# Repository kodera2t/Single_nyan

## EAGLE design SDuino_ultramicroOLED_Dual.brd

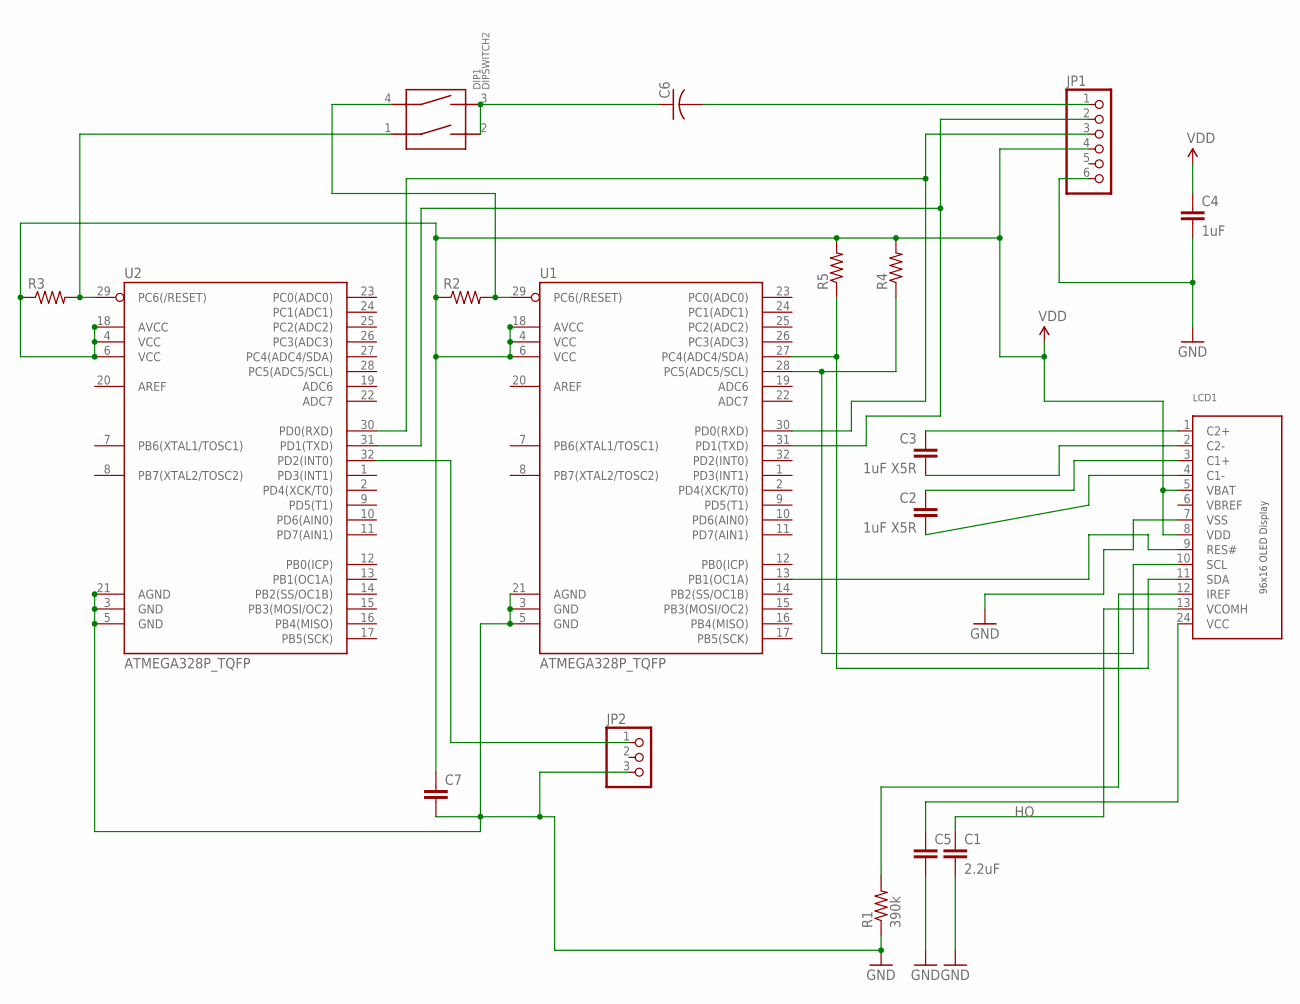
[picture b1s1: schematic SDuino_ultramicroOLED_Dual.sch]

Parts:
C1: 2.2uF; 0805
C2, C3: 1uF X5R; 0805
C4: 1uF; 0603-CAP
C5, C7: CC0603; C0603
C6: C-USC0603K; C0603K
DIP1: DIPSWITCH2
JP1: HEADER-1X6; 1X06_OVAL
JP2: HEADER-1X3; 1X03_OVAL
LCD1: DISP_OLED_UG-9616GLBBG02; UG-9616GLBBG02_0.65MM_WRAPAROUND
R1: 390k; 0603-RES
R2, R3, R4, R5: R-US_R0603; R0603
U1, U2: ATMEGA328P_TQFP; TQFP32-08

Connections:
C1N: C2.2, LCD1.4 (C1-)
C1P: C2.1, LCD1.3 (C1+)
C2N: C3.2, LCD1.2 (C2-)
C2P: C3.1, LCD1.1 (C2+)
GND: C1.2, C4.2, C5.2, C7.2, JP1.6, JP2.3, LCD1.7 (VSS), R1.1, U1.3 (GND), U1.5 (GND), U1.21 (AGND), U2.3 (GND), U2.5 (GND), U2.21 (AGND)
HO: C1.1, LCD1.13 (VCOMH)
IREF: LCD1.12 (IREF), R1.2
unnamed: LCD1.11 (SDA), R5.1, U1.27 (PC4(ADC4/SDA))
unnamed: DIP1.4, R2.2, U1.29 (PC6(/RESET))
unnamed: LCD1.9 (RES#), U1.13 (PB1(OC1A))
unnamed: JP2.1, U2.32 (PD2(INT0))
unnamed: LCD1.10 (SCL), R4.1, U1.28 (PC5(ADC5/SCL))
unnamed: DIP1.1, R3.2, U2.29 (PC6(/RESET))
unnamed: C6.1, DIP1.2, DIP1.3
unnamed: JP1.2, U1.31 (PD1(TXD)), U2.31 (PD1(TXD))
unnamed: JP1.3, U1.30 (PD0(RXD)), U2.30 (PD0(RXD))
unnamed: C6.2, JP1.1
VCOMH: C5.1, LCD1.24 (VCC)
VDD: C4.1, C7.1, JP1.4, LCD1.5 (VBAT), LCD1.8 (VDD), R2.1, R3.1, R4.2, R5.2, U1.4 (VCC), U1.6 (VCC), U1.18 (AVCC), U2.4 (VCC), U2.6 (VCC), U2.18 (AVCC)

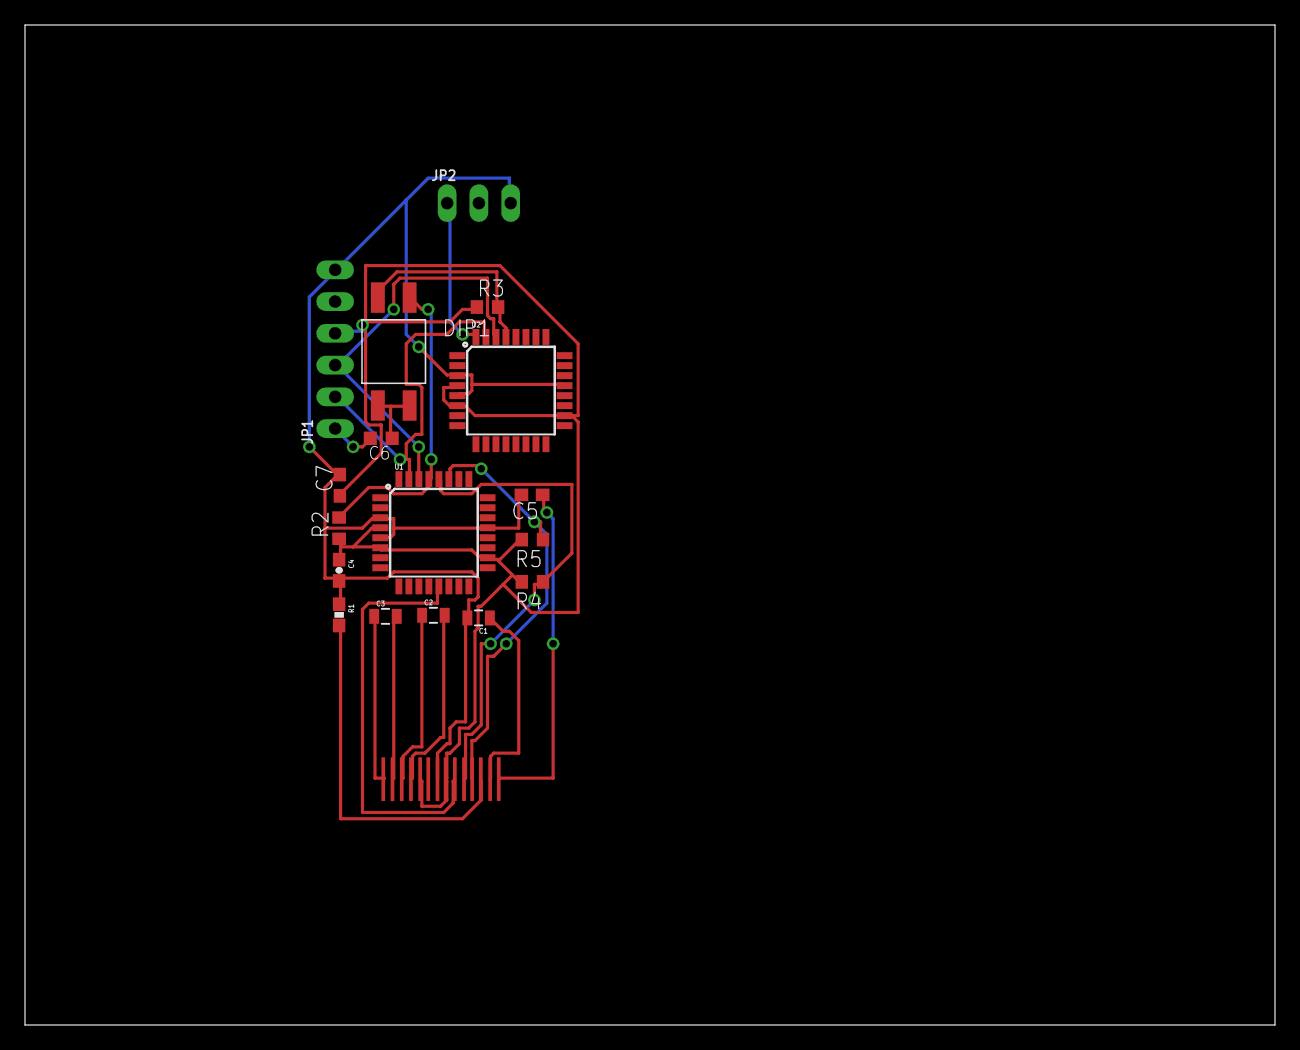
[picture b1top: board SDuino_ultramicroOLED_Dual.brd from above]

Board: 2 copper layers, 100.0 x 80.0 mm, 18 parts (1 on the bottom side), 19 nets.

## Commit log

2015-08-16 initial submission

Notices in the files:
parts and their libraries:
SparkFun-Passives: Licensing: Creative Commons ShareAlike 4.0 International - https://creativecommons.org/licenses/by-sa/4.0
OLED_mod: This work is placed in the public domain, and may be freely used for commercial and non-commercial work with the following conditions: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
